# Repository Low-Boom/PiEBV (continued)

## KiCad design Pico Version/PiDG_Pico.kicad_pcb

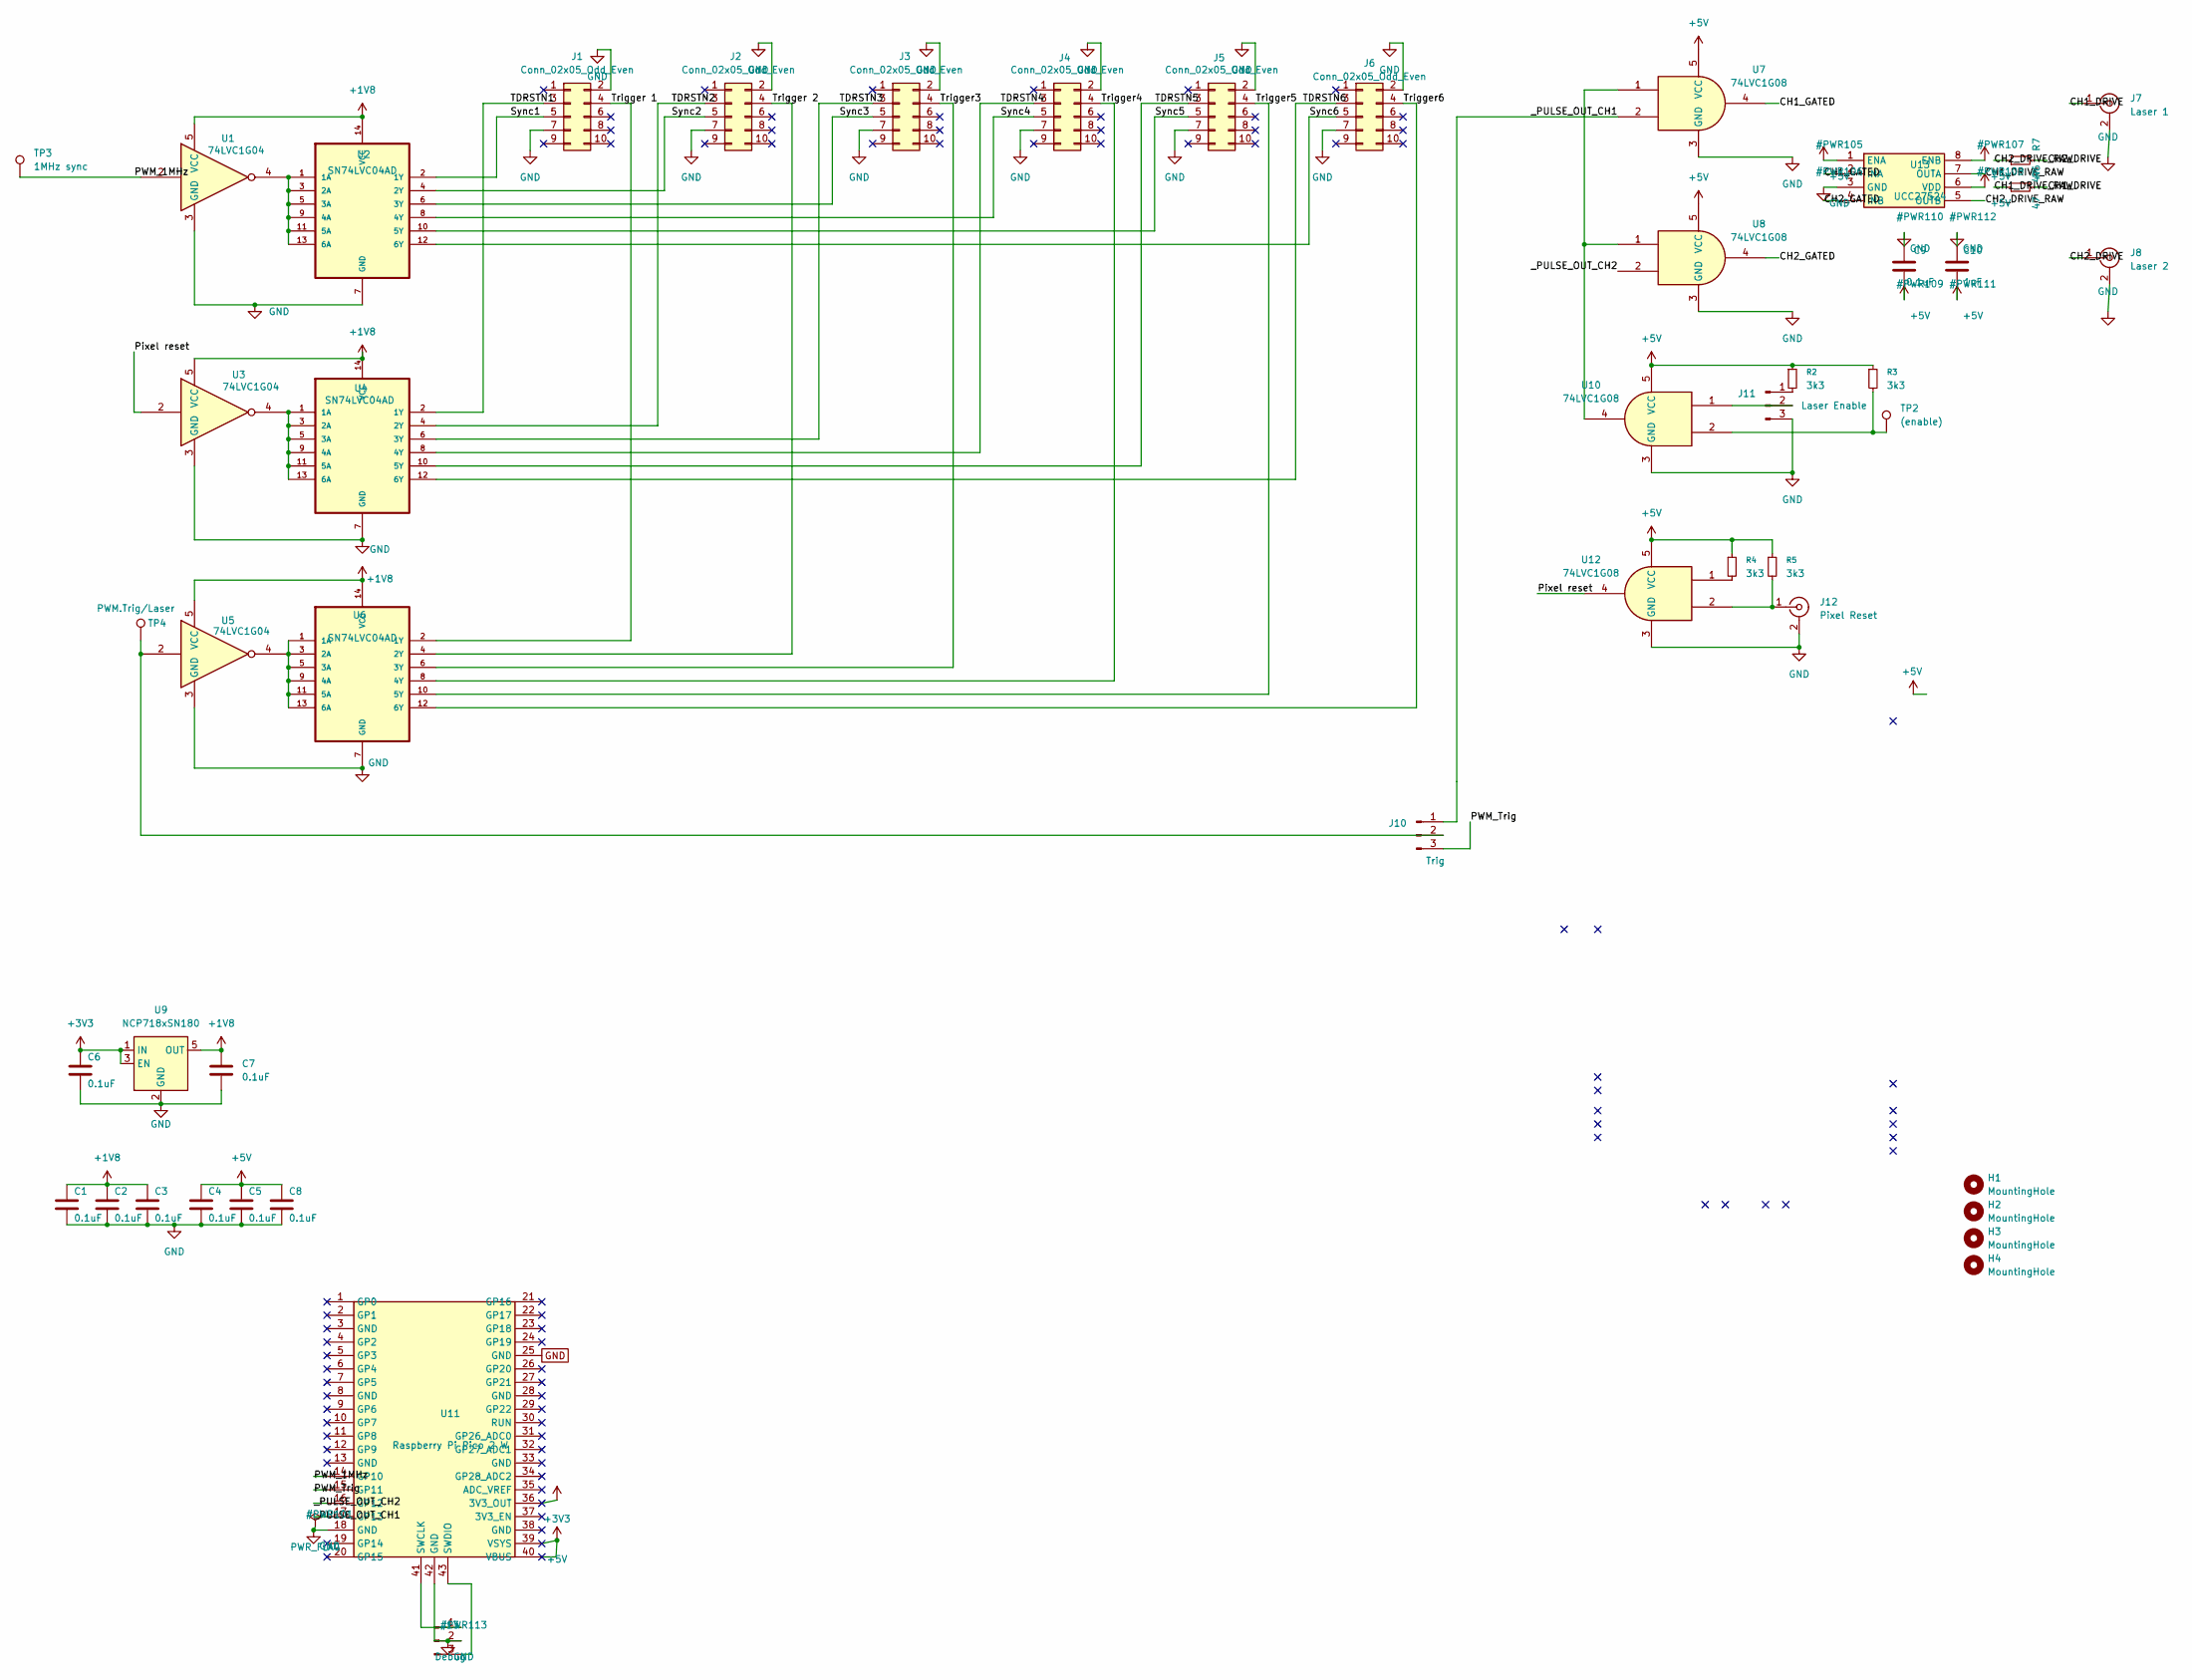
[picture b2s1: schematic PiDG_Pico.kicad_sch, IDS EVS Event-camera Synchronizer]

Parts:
C1, C2, C3, C4, C5, C6, C7, C8, C9: 0.1uF; C_0805_2012Metric_Pad1.18x1.45mm_HandSolder
C10: 1uF; C_0805_2012Metric_Pad1.18x1.45mm_HandSolder
H1, H2, H3, H4: MountingHole; MountingHole_3.2mm_M3_ISO14580
J1, J2, J3, J4, J5, J6: Conn_02x05_Odd_Even; IDC-Header_2x05_P2.54mm_Vertical
J7: Laser 1; BNC_Amphenol_B6252HB-NPP3G-50_Horizontal
J8: Laser 2; BNC_Amphenol_B6252HB-NPP3G-50_Horizontal
J10: Trig; PinHeader_1x03_P2.54mm_Vertical
J11: Laser Enable; PinHeader_1x03_P2.54mm_Vertical
J12: Pixel Reset; BNC_Amphenol_B6252HB-NPP3G-50_Horizontal
J13: Debug; PinHeader_1x03_P2.54mm_Vertical
R2, R3, R4, R5: 3k3; R_0805_2012Metric_Pad1.20x1.40mm_HandSolder
R6, R7: 47; R_0805_2012Metric_Pad1.20x1.40mm_HandSolder
TP2: (enable); PinHeader_1x01_P2.54mm_Horizontal
TP3: 1MHz sync; PinHeader_1x01_P2.54mm_Horizontal
TP4: PWM.Trig/Laser; PinHeader_1x01_P2.54mm_Horizontal
U1, U3, U5: 74LVC1G04; SOT-23-5_HandSoldering
U2, U4, U6: SN74LVC04AD; SOIC127P600X175-14N
U7, U8, U10, U12: 74LVC1G08; SOT-23-5_HandSoldering
U9: NCP718xSN180; SOT-23-5
U11: Raspberry Pi Pico 2 W; RPi_Pico2W_SMD_TH
U13: UCC27524; SOIC-8_3.9x4.9mm_P1.27mm

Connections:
+1V8: C1.1, C2.1, C3.1, C7.1, U1.5 (VCC), U2.14 (VCC), U3.5 (VCC), U4.14 (VCC), U5.5 (VCC), U6.14 (VCC), U9.5 (OUT)
+3V3: C6.1, U9.1 (IN), U9.3 (EN), U11.36 (3V3_OUT)
+5V: C4.1, C5.1, C8.1, C9.2, C10.2, R2.1, R3.1, R4.1, R5.1, U7.5 (VCC), U8.5 (VCC), U10.5 (VCC), U11.39 (VSYS), U11.40 (VBUS), U12.5 (VCC), U13.1 (ENA), U13.6 (VDD), U13.8 (ENB)
CH1_DRIVE: J7.1 (In), R6.2
CH1_DRIVE_RAW: R6.1, U13.7 (OUTA)
CH1_GATED: U7.4, U13.2 (INA)
CH2_DRIVE: J8.1 (In), R7.2
CH2_DRIVE_RAW: R7.1, U13.5 (OUTB)
CH2_GATED: U8.4, U13.4 (INB)
GND: C1.2, C2.2, C3.2, C4.2, C5.2, C6.2, C7.2, C8.2, C9.1, C10.1, J1.2, J1.7, J2.2, J2.7, J3.2, J3.7, J4.2, J4.7, J5.2, J5.7, J6.2, J6.7, J7.2 (Ext), J8.2 (Ext), J11.3, J12.2 (Ext), J13.2, U1.3 (GND), U2.7 (GND), U3.3 (GND), U4.7 (GND), U5.3 (GND), U6.7 (GND), U7.3 (GND), U8.3 (GND), U9.2 (GND), U10.3 (GND), U11.18 (GND), U11.25 (GND), U11.42 (GND), U12.3 (GND), U13.3 (GND)
unnamed: J1.3, U4.2 (1Y)
unnamed: J1.5, U2.2 (1Y)
unnamed: J2.3, U4.4 (2Y)
unnamed: J2.5, U2.4 (2Y)
unnamed: J3.3, U4.6 (3Y)
unnamed: J3.5, U2.6 (3Y)
unnamed: J4.3, U4.8 (4Y)
unnamed: J4.5, U2.8 (4Y)
unnamed: J5.3, U4.10 (5Y)
unnamed: J6.3, U4.12 (6Y)
unnamed: J10.2, TP4.1, U5.2
unnamed: J11.2, U10.1
unnamed: J11.1, R2.2
unnamed: J12.1 (In), R5.2, U12.2
unnamed: J13.1, U11.41 (SWCLK)
unnamed: J13.3, U11.43 (SWDIO)
unnamed 27: R3.2, TP2.1, U10.2; also elsewhere on the board
unnamed: R4.2, U12.1
unnamed: U1.4, U2.1 (1A), U2.3 (2A), U2.5 (3A), U2.9 (4A), U2.11 (5A), U2.13 (6A)
unnamed: U3.4, U4.1 (1A), U4.3 (2A), U4.5 (3A), U4.9 (4A), U4.11 (5A), U4.13 (6A)
unnamed: U5.4, U6.1 (1A), U6.3 (2A), U6.5 (3A), U6.9 (4A), U6.11 (5A), U6.13 (6A)
unnamed: U7.1, U8.1, U10.4
PWM_Trig: J10.3, U11.15 (GP11)
Pixel reset: U3.2, U12.4
Sync5: J5.5, U2.10 (5Y)
Sync6: J6.5, U2.12 (6Y)
Trigger3: J3.4, U6.6 (3Y)
Trigger4: J4.4, U6.8 (4Y)
Trigger5: J5.4, U6.10 (5Y)
Trigger6: J6.4, U6.12 (6Y)
Trigger 1: J1.4, U6.2 (1Y)
Trigger 2: J2.4, U6.4 (2Y)
_PULSE_OUT_CH1: J10.1, U7.2, U11.17 (GP13)
_PULSE_OUT_CH2: U8.2, U11.16 (GP12)

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
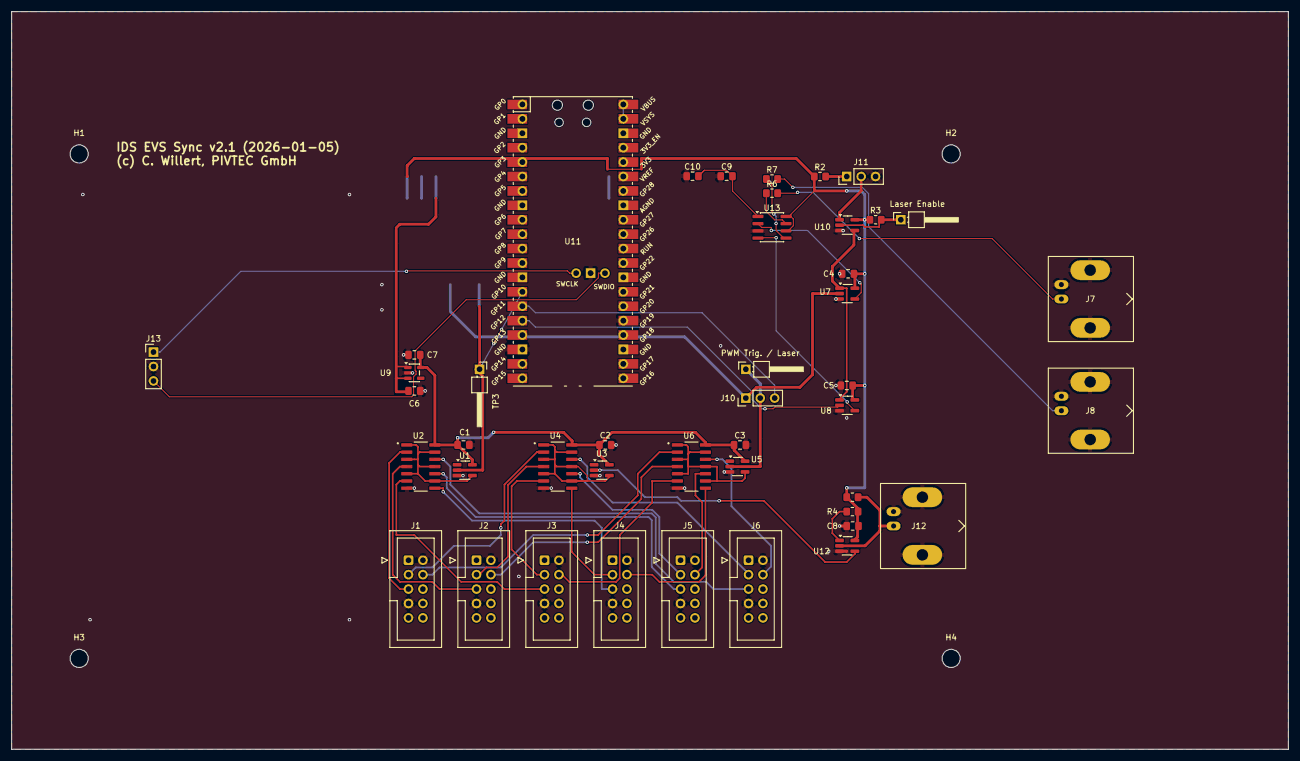
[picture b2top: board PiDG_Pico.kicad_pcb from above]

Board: 2 copper layers, 225.0 x 130.0 mm, 48 parts (0 on the bottom side), 45 nets.

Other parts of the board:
Laser Enable: (enable); PinHeader_1x01_P2.54mm_Horizontal
PWM Trig. / Laser: PWM.Trig/Laser; PinHeader_1x01_P2.54mm_Horizontal

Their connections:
unnamed 27: Laser Enable.1; also elsewhere on the board

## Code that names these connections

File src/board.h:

#pragma once
// GPIO assignments of the PiEBV 4-layer board. These MUST match
// "PiEBV_Pico.kicad_sch" (repo root). The Pico plugs into sockets
// J14/J15; J14 pad n = Pico physical pin n.
//
//   constant     GPIO   Pico pin   J14 pad   board net         drives
//   ----------   ----   --------   -------   ---------------   ---------------------------------
//   kPinMarker   GP11      15         15     PWM_Trig          J10.3 -> U5 -> U6 -> Trigger1..6, and
//                                                                U19 -> J12 (External Sync Out)
//   kPinCh2      GP12      16         16     _PULSE_OUT_CH2    U8 -> U13 -> J8 (Laser 2); R18 10k to GND
//   kPinCh1      GP13      17         17     _PULSE_OUT_CH1    U7 -> U13 -> J7 (Laser 1); R17 10k to GND
//   kPinSync     GP15      20         20     PWM_1MHz          U1 -> U2 -> Sync1..6, TP3. clk_gpout1, not PIO:
//                                                                only GP13/15/21 (23-25 internal) have a clock
//                                                                output, and GP13 is CH1 (sync_clock.h).
//   kPinPixGate  GP16      21    J15 pad 20 PIXRST_GATE       U3 pins 1+2 (NAND as inverter) -> U4 ->
//                                                                TDRSTN1..6; R24 10k to +3V3. Driven INVERTED
//                                                                (main.cpp): PIO latch high = pixels in reset.
//   kPinClockSel GP10      14         14     CLK_SEL           R29 1k -> J20.1 (J20.2 = GND). Clock jumper, read once
//                                                                at boot (clock_mode.cpp): fitted = 300 MHz, open = 150 MHz.
//                                                                Internal pull-up only; no capacitor on the net. R29
//                                                                limits the current if GP10 is driven with the shunt fitted.
//   kPinArmedLed GP17      22    J15 pad 19 ARMED_LED         Q2 gate (R38 100k to GND) -> D3 "ARMED" (Rev 2 board). HIGH while
//                                                                ARMED. D3 lights only if J11 is closed and +12 V is good as
//                                                                well (LASER_EN -> D3 -> Q2 -> Q1). Status only: it gates nothing.
//
// CH1 is the HIGHER GPIO and CH2 the lower. The order is deliberate, so do not
// "tidy" these into ascending order.
// GP2-GP5 are not connected on this board. GP17 is not connected on the Rev 1 board (driving it there is harmless). GP10 (SYNC before it moved to the clock generator)
// is now the clock jumper input.

constexpr unsigned kPinMarker = 11;
constexpr unsigned kPinCh2 = 12;
constexpr unsigned kPinCh1 = 13;
constexpr unsigned kPinSync = 15;
constexpr unsigned kPinPixGate = 16;
constexpr unsigned kPinClockSel = 10;
constexpr unsigned kPinArmedLed = 17;

constexpr unsigned kLaserPinMask = (1u << kPinCh1) | (1u << kPinCh2);
